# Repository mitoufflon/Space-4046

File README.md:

# Space-4046
Crazy synth  from synaesthesia http://electro-music.com/forum/topic-63269.html

more info : https://wiki.labomedia.org/index.php/Space-4046

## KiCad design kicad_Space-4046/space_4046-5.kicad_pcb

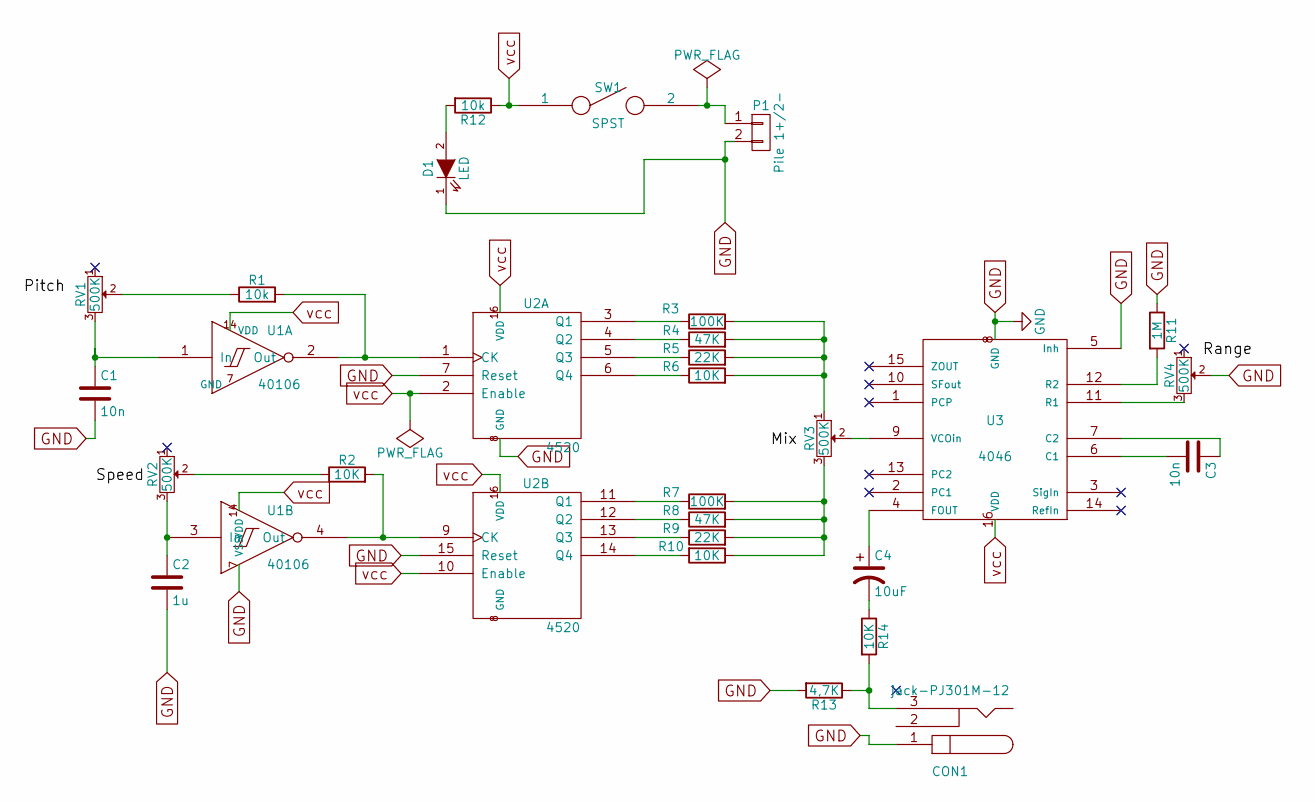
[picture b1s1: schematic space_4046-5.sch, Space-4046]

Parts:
C1, C3: 10n; C_Disc_D6_P5
C2: 1u; C_Disc_D6_P5
C4: 10uF; C_Radial_D5_L6_P2.5
CON1: jack-PJ301M-12; PJ301M-12
D1: LED; LED-5MM
P1: Pile 1+/2-; bornier2
R1, R12: 10k; Resistor_Horizontal_RM7mmPrint
R2, R6, R10, R14: 10K; Resistor_Horizontal_RM7mmPrint
R3, R7: 100K; Resistor_Horizontal_RM7mmPrint
R4, R8: 47K; Resistor_Horizontal_RM7mmPrint
R5, R9: 22K; Resistor_Horizontal_RM7mmPrint
R11: 1M; Resistor_Horizontal_RM7mmPrint
R13: 4,7K; Resistor_Horizontal_RM7mmPrint
RV1, RV2, RV3, RV4: 500K; Potentiometer_Alpha-RV09
SW1: SPST; SW_DIP_x1_Slide
U1: 40106; DIP-14_W7.62mm_LongPads
U2: 4520; DIP-16_W7.62mm_LongPads
U3: 4046; DIP-16_W7.62mm_LongPads

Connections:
GND: C1.2, C2.2, CON1.1, D1.1 (K), P1.2, R11.1, R13.2, RV4.2, U1.7 (GND), U2.7 (Reset), U2.8 (GND), U2.15 (Reset), U3.5 (Inh), U3.8 (GND)
unnamed: C1.1, RV1.3, U1.1 (In)
unnamed: C2.1, RV2.3, U1.3 (In)
unnamed: C3.1, U3.7 (C2)
unnamed: C3.2, U3.6 (C1)
unnamed: C4.1, U3.4 (FOUT)
unnamed: C4.2, R14.1
unnamed: CON1.3, R13.1, R14.2
unnamed: D1.2 (A), R12.2
unnamed: P1.1, SW1.2
unnamed: R1.1, RV1.2
unnamed: R1.2, U1.2 (Out), U2.1 (CK)
unnamed: R2.1, RV2.2
unnamed: R2.2, U1.4 (Out), U2.9 (CK)
unnamed: R3.1, U2.3 (Q1)
unnamed: R3.2, R4.2, R5.2, R6.2, RV3.1
unnamed: R4.1, U2.4 (Q2)
unnamed: R5.1, U2.5 (Q3)
unnamed: R6.1, U2.6 (Q4)
unnamed: R7.1, U2.11 (Q1)
unnamed: R8.1, U2.12 (Q2)
unnamed: R9.1, U2.13 (Q3)
unnamed: R7.2, R8.2, R9.2, R10.1, RV3.3
unnamed: R10.2, U2.14 (Q4)
unnamed: R11.2, U3.12 (R2)
unnamed: RV3.2, U3.9 (VCOin)
unnamed: RV4.3, U3.11 (R1)
vcc: R12.1, SW1.1, U1.14 (VDD), U2.2 (Enable), U2.10 (Enable), U2.16 (VDD), U3.16 (VDD)

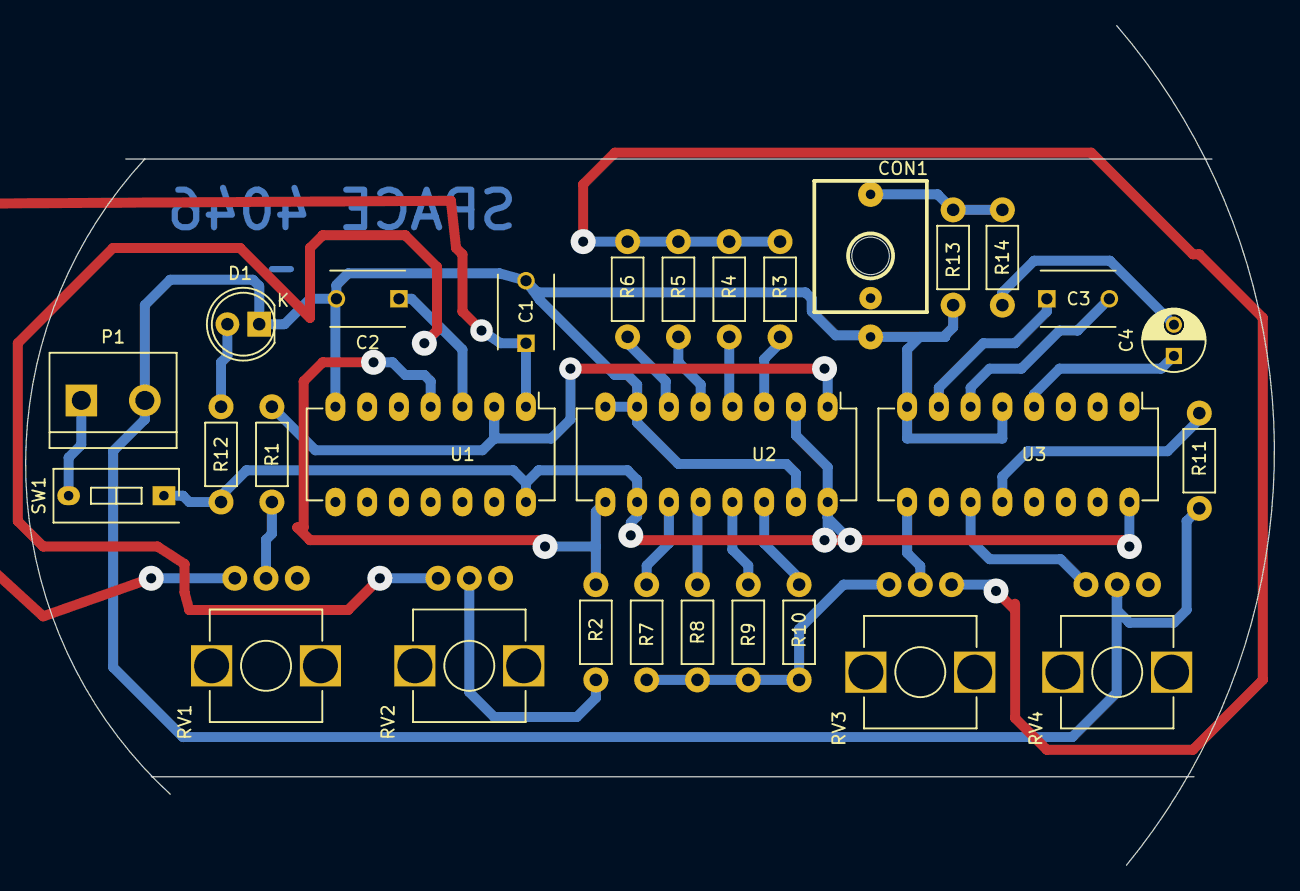
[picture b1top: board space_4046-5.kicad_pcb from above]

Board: 2 copper layers, 99.9 x 67.1 mm, 29 parts (0 on the bottom side), 28 nets.

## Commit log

2018-02-20 Update README.md
    add image + link
2018-02-20 Add files via upload
    Add kicad files...Need cleaning...
